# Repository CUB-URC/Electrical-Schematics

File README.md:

Vault of Schematics for Custom Circuits and Components used by the Electrical Hardware Subteam

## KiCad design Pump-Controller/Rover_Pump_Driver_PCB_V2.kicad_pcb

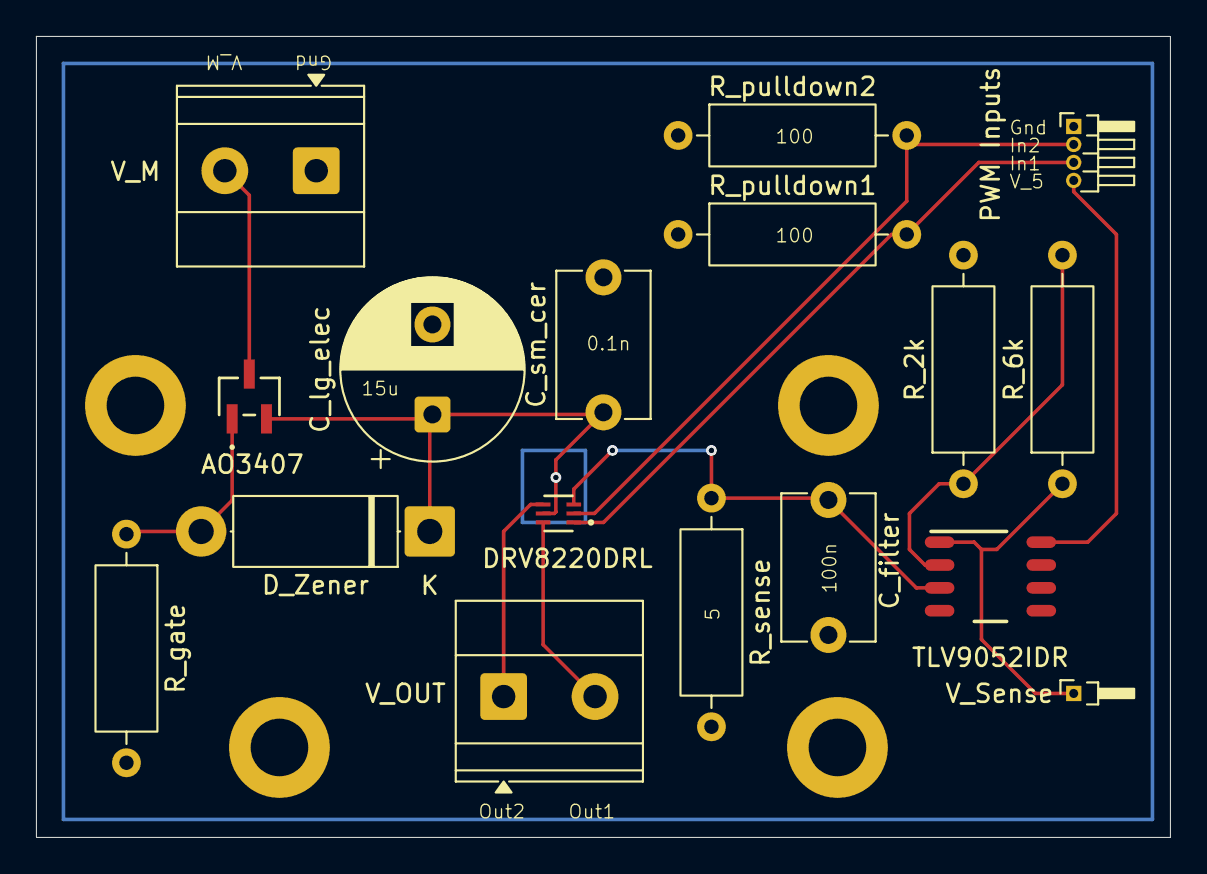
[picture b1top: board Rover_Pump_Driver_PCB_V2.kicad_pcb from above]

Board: 2 copper layers, 63.0 x 44.5 mm, 17 parts (0 on the bottom side), 10 nets.

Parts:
AO3407: SOT-23-3L_AOS; SOT-23-3L_AOS-M
C_filter: C_Disc_D8.0mm_W5.0mm_P7.50mm
C_lg_elec: CP_Radial_D10.0mm_P5.00mm
C_sm_cer: C_Disc_D8.0mm_W5.0mm_P7.50mm
DRV8220DRL: SOT5X3-6_DRL_TEX; SOT5X3-6_DRL_TEX-M
D_Zener: D_5W_P12.70mm_Horizontal
PWM Inputs: PinHeader_1x04_P1.00mm_Horizontal
R_2k, R_6k: R_Axial_DIN0309_L9.0mm_D3.2mm_P12.70mm_Horizontal
R_gate: R_Axial_DIN0309_L9.0mm_D3.2mm_P12.70mm_Horizontal
R_pulldown1, R_pulldown2: R_Axial_DIN0309_L9.0mm_D3.2mm_P12.70mm_Horizontal
R_sense: R_Axial_DIN0309_L9.0mm_D3.2mm_P12.70mm_Horizontal
TLV9052IDR: D0008A_N; D0008A_M
V_M: TerminalBlock_Phoenix_MKDS-1,5-2-5.08_1x02_P5.08m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; TerminalBlock_Phoenix_MKDS-1,5-2-5.08_1x02_P5.08mm_Horizont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
V_OUT: TerminalBlock_Phoenix_MKDS-1,5-2-5.08_1x02_P5.08m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; TerminalBlock_Phoenix_MKDS-1,5-2-5.08_1x02_P5.08mm_Horizont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
V_Sense: PinHeader_1x01_P1.00mm_Horizontal

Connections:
V_5: PWM Inputs.4, TLV9052IDR.8
V_M: AO3407.2, AO3407.3, C_lg_elec.1, C_sm_cer.1, DRV8220DRL.5, D_Zener.1, V_M.2
V_sense: R_2k.1, R_6k.1, R_6k.2, TLV9052IDR.1, TLV9052IDR.2, V_Sense.1
V_sense_in: C_filter.1, DRV8220DRL.3, R_sense.1, TLV9052IDR.3
V_z: AO3407.1, D_Zener.2, R_gate.1
gnd: C_filter.2, C_lg_elec.2, C_sm_cer.2, PWM Inputs.1, R_2k.2, R_gate.2, R_pulldown1.1, R_pulldown2.1, R_sense.2, TLV9052IDR.4, V_M.1
in1: DRV8220DRL.1, PWM Inputs.3, R_pulldown1.2
in2: DRV8220DRL.2, PWM Inputs.2, R_pulldown2.2
out1: DRV8220DRL.6, V_OUT.2
out2: DRV8220DRL.4, V_OUT.1
